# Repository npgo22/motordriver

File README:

A motor driver PCB for a personal project of mine. First ever KiCAD project, revised on 9/15/2025.

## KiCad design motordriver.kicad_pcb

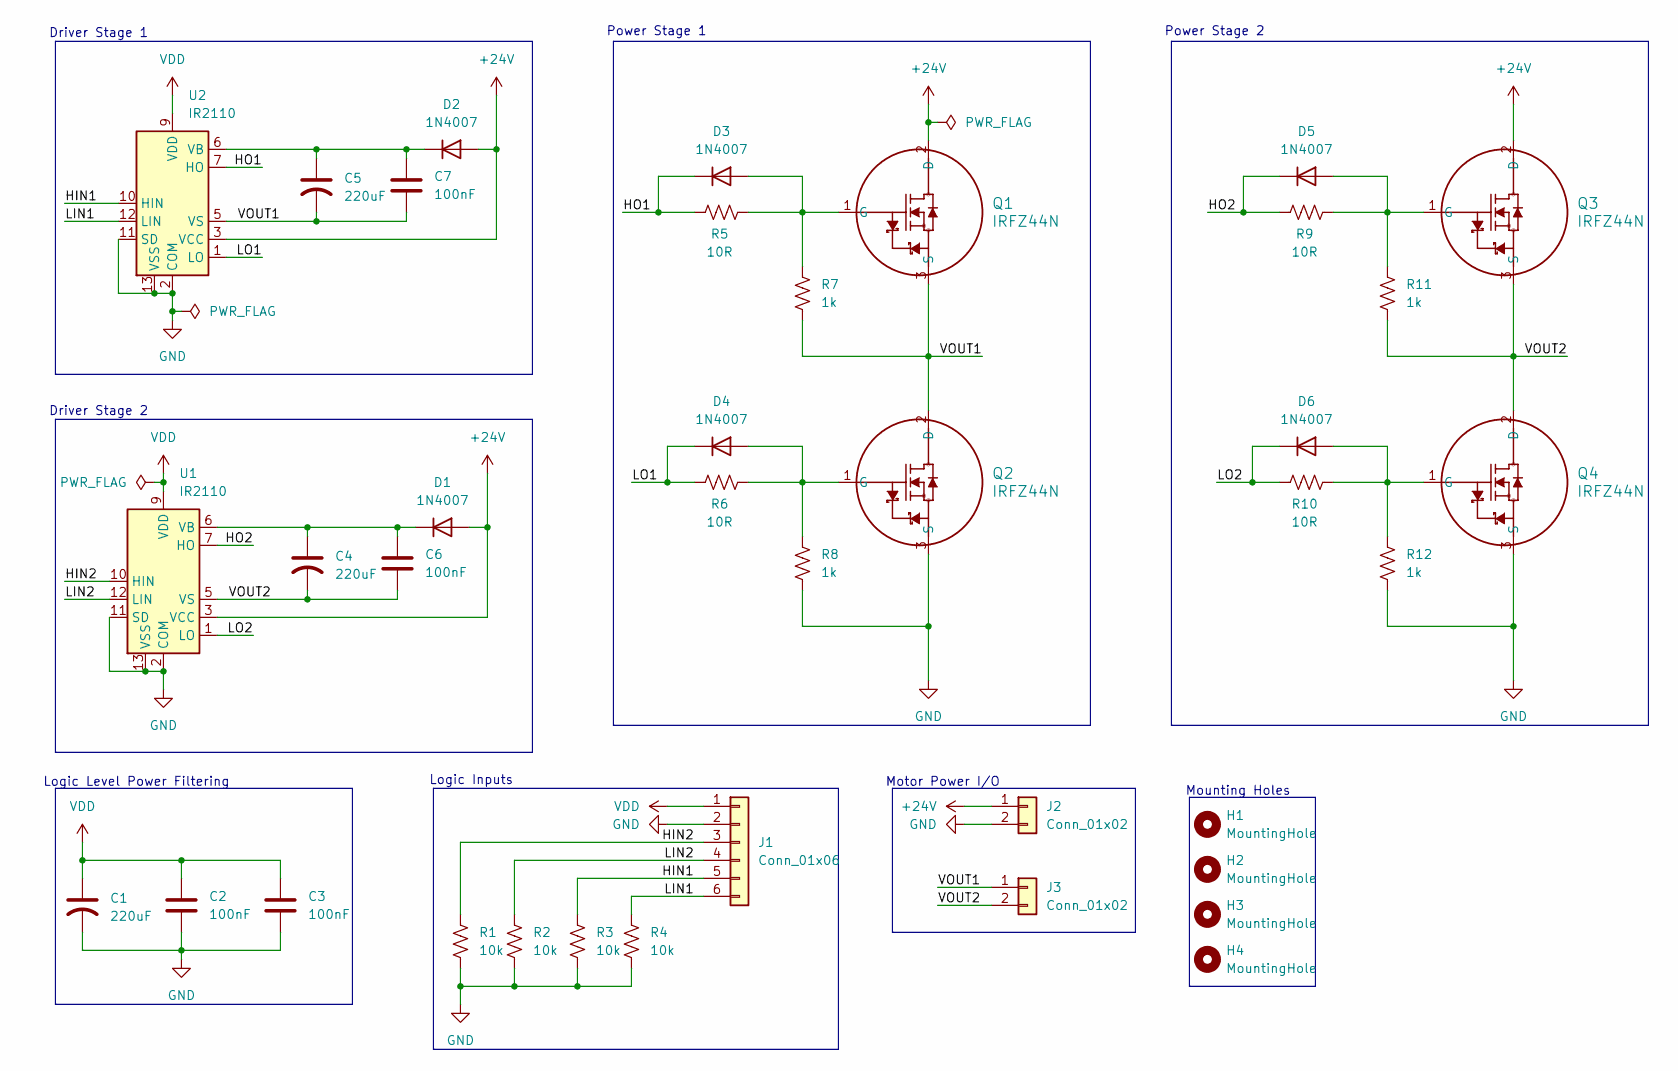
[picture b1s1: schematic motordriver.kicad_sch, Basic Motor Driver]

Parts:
C1, C4, C5: 220uF; CP_Radial_D6.3mm_P2.50mm; LCSC C371103
C2, C3, C6, C7: 100nF; C_Disc_D5.1mm_W3.2mm_P5.00mm; LCSC C2761728
D1, D2, D3, D4, D5, D6: 1N4007; D_DO-41_SOD81_P10.16mm_Horizontal; LCSC C53568
H1, H2, H3, H4: MountingHole; MountingHole_3.2mm_M3
J1: Conn_01x06; PinHeader_1x06_P2.54mm_Vertical; LCSC C7501270
J2, J3: Conn_01x02; PhoenixContact_MSTBA_2,5_2-G_1x02_P5.00mm_Horizontal; LCSC C90074
Q1, Q2, Q3, Q4: IRFZ44N; TO-220-3_Vertical; LCSC C2586
R1, R2, R3, R4: 10k; R_Axial_DIN0207_L6.3mm_D2.5mm_P10.16mm_Horizontal; LCSC C119347
R5, R6, R9, R10: 10R; R_Axial_DIN0207_L6.3mm_D2.5mm_P10.16mm_Horizontal; LCSC C119282
R7, R8, R11, R12: 1k; R_Axial_DIN0207_L6.3mm_D2.5mm_P10.16mm_Horizontal; LCSC C119324
U1, U2: IR2110; DIP-14_W7.62mm; LCSC C20623179

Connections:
+24V: D1.2 (A), D2.2 (A), J2.1, Q1.2 (D), Q3.2 (D), U1.3 (VCC), U2.3 (VCC)
/HIN1: J1.5, R3.1, U2.10 (HIN)
/HIN2: J1.3, R1.1, U1.10 (HIN)
/HO1: D3.1 (K), R5.1, U2.7 (HO)
/HO2: D5.1 (K), R9.1, U1.7 (HO)
/LIN1: J1.6, R4.1, U2.12 (LIN)
/LIN2: J1.4, R2.1, U1.12 (LIN)
/LO1: D4.1 (K), R6.1, U2.1 (LO)
/LO2: D6.1 (K), R10.1, U1.1 (LO)
/VOUT1: C5.2, C7.2, J3.1, Q1.3 (S), Q2.2 (D), R7.2, U2.5 (VS)
/VOUT2: C4.2, C6.2, J3.2, Q3.3 (S), Q4.2 (D), R11.2, U1.5 (VS)
GND: C1.2, C2.2, C3.2, J1.2, J2.2, Q2.3 (S), Q4.3 (S), R1.2, R2.2, R3.2, R4.2, R8.2, R12.2, U1.2 (COM), U1.11 (SD), U1.13 (VSS), U2.2 (COM), U2.11 (SD), U2.13 (VSS)
unnamed: C4.1, C6.1, D1.1 (K), U1.6 (VB)
unnamed: C5.1, C7.1, D2.1 (K), U2.6 (VB)
unnamed: D3.2 (A), Q1.1 (G), R5.2, R7.1
unnamed: D4.2 (A), Q2.1 (G), R6.2, R8.1
unnamed: D5.2 (A), Q3.1 (G), R9.2, R11.1
unnamed: D6.2 (A), Q4.1 (G), R10.2, R12.1
VDD: C1.1, C2.1, C3.1, J1.1, U1.9 (VDD), U2.9 (VDD)

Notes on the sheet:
Power Stage 2
Driver Stage 2
Driver Stage 1
Mounting Holes
Logic Inputs
Power Stage 1
Motor Power I/O
Logic Level Power Filtering

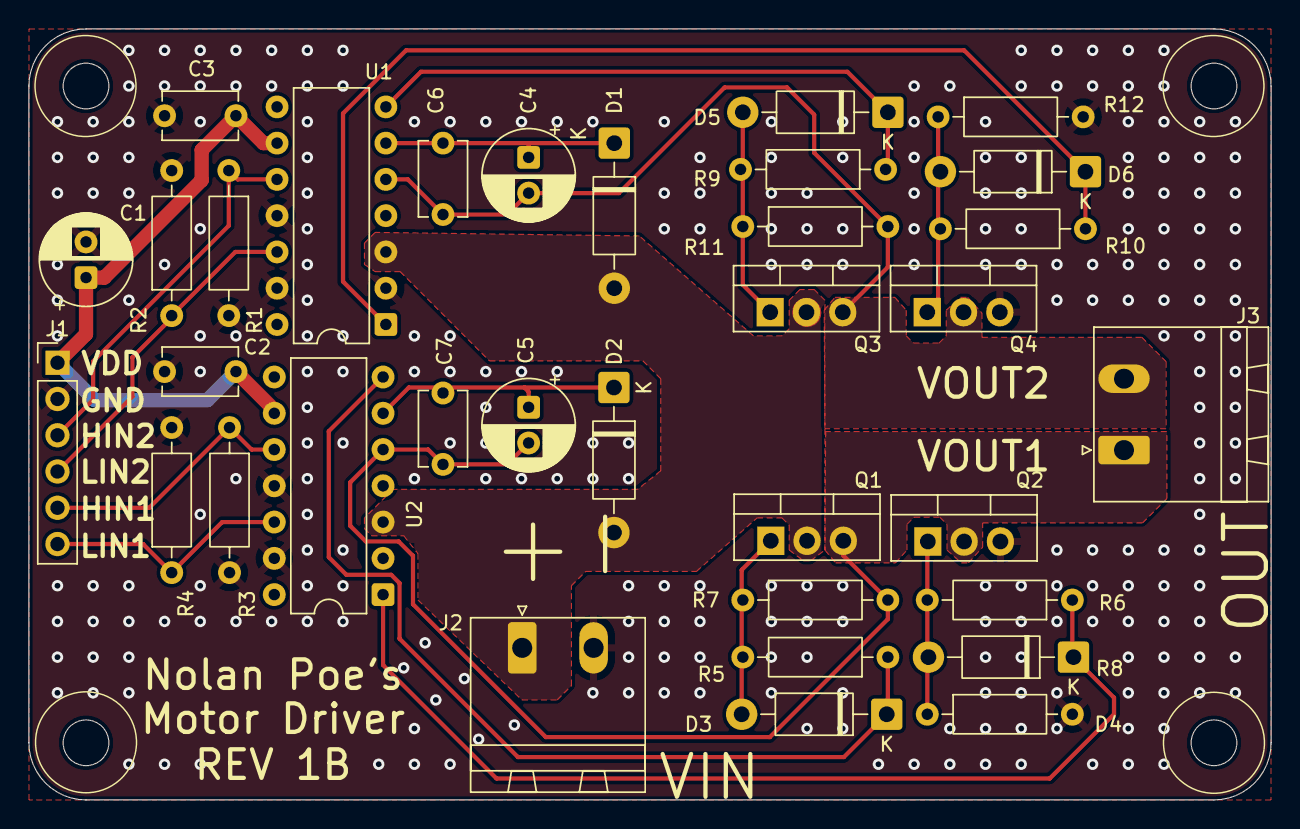
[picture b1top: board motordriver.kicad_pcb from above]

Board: 2 copper layers, 87.0 x 54.0 mm, 38 parts (0 on the bottom side), 19 nets.

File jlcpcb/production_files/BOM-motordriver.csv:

Comment,Designator,Footprint,LCSC,Quantity
10R,"R10,R5,R6,R9",R_Axial_DIN0207_L6.3mm_D2.5mm_P10.16mm_Horizontal,C119282,4
1k,"R11,R12,R7,R8",R_Axial_DIN0207_L6.3mm_D2.5mm_P10.16mm_Horizontal,C119324,4
10k,"R1,R2,R3,R4",R_Axial_DIN0207_L6.3mm_D2.5mm_P10.16mm_Horizontal,C119347,4
IR2110,"U1,U2",DIP-14_W7.62mm,C20623179,2
IRFZ44N,"Q1,Q2,Q3,Q4",TO-220-3_Vertical,C2586,4
100nF,"C2,C3,C6,C7",C_Disc_D5.1mm_W3.2mm_P5.00mm,C2761728,4
220uF,"C1,C4,C5",CP_Radial_D6.3mm_P2.50mm,C371103,3
1N4007,"D1,D2,D3,D4,D5,D6",D_DO-41_SOD81_P10.16mm_Horizontal,C53568,6
Conn_01x06,J1,PinHeader_1x06_P2.54mm_Vertical,C7501270,1
Conn_01x02,"J2,J3","PhoenixContact_MSTBA_2,5_2-G_1x02_P5.00mm_Horizontal",C90074,2

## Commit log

2025-09-16 Add README
